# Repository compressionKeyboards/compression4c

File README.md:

# compression (4c)
PCB, ergogen, kicad files for 4c wireless split ergo keyboard

This repo contains the files to order a custom PCB for chocBoard, checkout the [zmk layout](https://github.com/compressionKeyboards/4c-zmk-layout) to build firmware!

Read more about chocBoard on [compression](https://compressionkeyboards.com).

## Downloads
feel free to dig around in my working files in the repo :) but if you just want to order a PCB or print a case, checkout the releases tab.

## TODO
Fusion and STEP files will be added soon, I'm just cleaning them up a bit. Also, display cover files are not final, and just a few dimensions will be tweaked in an upcoming release.

## LICENSE
This repo is attached with Attribution-NonCommercial-ShareAlike 4.0 International Creative Commons License, learn what his means [here](https://creativecommons.org/licenses/by-nc-sa/4.0/).

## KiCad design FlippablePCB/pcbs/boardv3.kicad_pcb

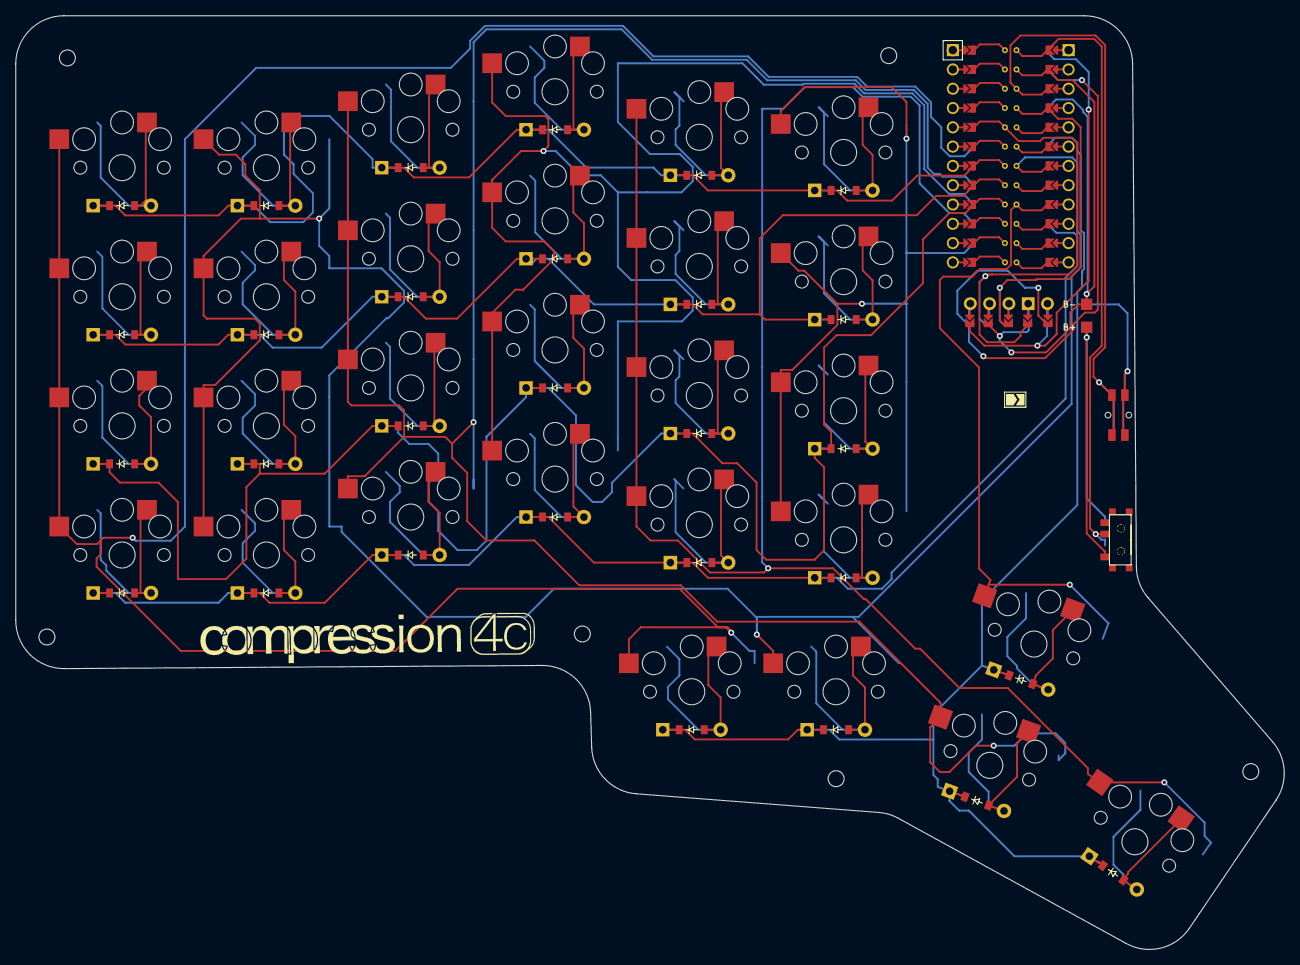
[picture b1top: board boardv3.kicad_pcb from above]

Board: 2 copper layers, 167.0 x 122.9 mm, 64 parts (0 on the bottom side), 43 nets.

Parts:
D1, D2, D3, D4, D5, D6, D7, D8, D9, D10, D11, D12, D13, D14, D15, D16, D17, D18, D19, D20, D21, D22, D23, D24, D25, D26, D27, D28, D29: ComboDiode
MCU1: ProMicro
OLED1: OLED; OLED_headers
PAD1, PAD2: SMDPad
S1, S2, S3, S4, S5, S6, S7, S8, S9, S10, S11, S12, S13, S14, S15, S16, S17, S18, S19, S20, S21, S22, S23, S24, S25, S26, S27, S28, S29: PG1350
T1, T2: SPDT_C128955

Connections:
Bplus: PAD1.1, T1.1, T2.1
GND: MCU1.2, MCU1.21, MCU1.22, PAD2.1
P3: D25.1, D26.1, D27.1, D28.1, D29.1, MCU1.19
P4: D4.1, D8.1, D12.1, D16.1, D20.1, D24.1, MCU1.18
P5: D3.1, D7.1, D11.1, D15.1, D19.1, D23.1, MCU1.17
P6: D2.1, D6.1, D10.1, D14.1, D18.1, D22.1, MCU1.16
P7: D1.1, D5.1, D9.1, D13.1, D17.1, D21.1, MCU1.15
P14: MCU1.10, S17.2, S18.2, S19.2, S20.2, S29.2
P15: MCU1.9, S13.2, S14.2, S15.2, S16.2, S28.2
P16: MCU1.11, S21.2, S22.2, S23.2, S24.2
P18: MCU1.8, S9.2, S10.2, S11.2, S12.2, S27.2
P19: MCU1.7, S5.2, S6.2, S7.2, S8.2, S26.2
P20: MCU1.6, S1.2, S2.2, S3.2, S4.2, S25.2
RAW: MCU1.1, T1.2, T2.2
far_home: D29.2, S29.1
home_home: D27.2, S27.1
home_top: D28.2, S28.1
index_bottom: D17.2, S17.1
index_home: D18.2, S18.1
index_num: D20.2, S20.1
index_top: D19.2, S19.1
inner_bottom: D21.2, S21.1
inner_home: D22.2, S22.1
inner_num: D24.2, S24.1
inner_top: D23.2, S23.1
middle_bottom: D13.2, S13.1
middle_home: D14.2, S14.1
middle_num: D16.2, S16.1
middle_top: D15.2, S15.1
near1_home: D25.2, S25.1
near2_home: D26.2, S26.1
outer_bottom: D1.2, S1.1
outer_home: D2.2, S2.1
outer_num: D4.2, S4.1
outer_top: D3.2, S3.1
pinky_bottom: D5.2, S5.1
pinky_home: D6.2, S6.1
pinky_num: D8.2, S8.1
pinky_top: D7.2, S7.1
ring_bottom: D9.2, S9.1
ring_home: D10.2, S10.1
ring_num: D12.2, S12.1
ring_top: D11.2, S11.1

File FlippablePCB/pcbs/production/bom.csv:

Designator,Footprint,Quantity,Value,LCSC Part #
"_24, _23, _22, _21, _20, _19, _18, _17, _16, _15, _14, _13, _12, _11, _10, _9, _8, _7, _6, _5, _4, _3, _2, ",,24,,
"D1, D10, D11, D12, D13, D14, D15, D16, D17, D18, D19, D2, D20, D21, D22, D23, D24, D25, D26, D27, D28, D29, D3, D4, D5, D6, D7, D8, D9",ComboDiode,29,,
MCU1,ProMicro,1,,
OLED1,OLED_headers,1,OLED,
"PAD1, PAD2",SMDPad,2,,
"S1, S10, S11, S12, S13, S14, S15, S16, S17, S18, S19, S2, S20, S21, S22, S23, S24, S25, S26, S27, S28, S29, S3, S4, S5, S6, S7, S8, S9",PG1350,29,,
"T1, T2",SPDT_C128955,2,,

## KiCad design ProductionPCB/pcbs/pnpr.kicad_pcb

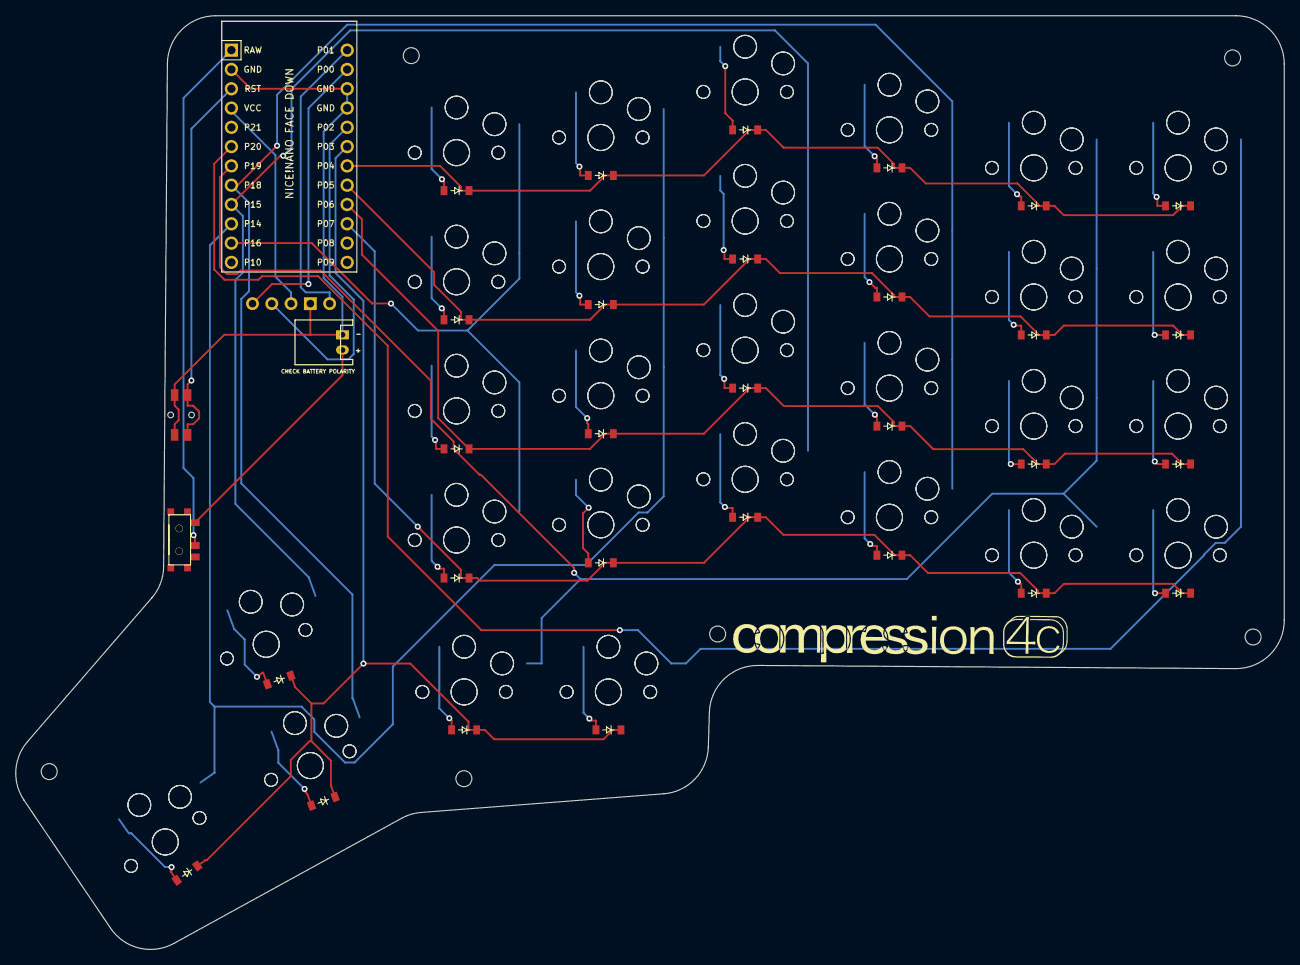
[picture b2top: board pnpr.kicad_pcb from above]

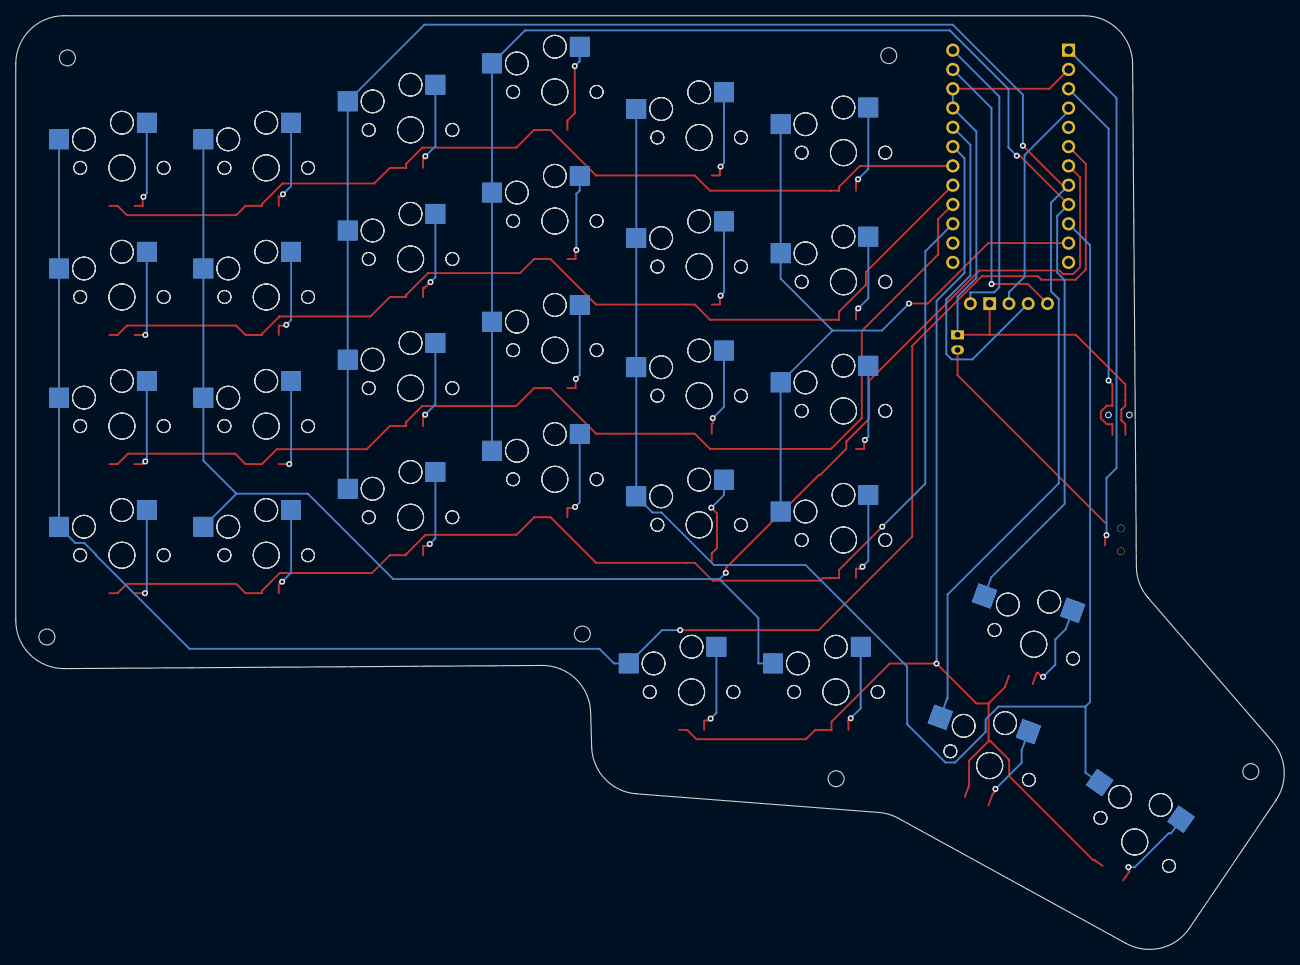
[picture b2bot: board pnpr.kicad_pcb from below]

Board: 2 copper layers, 167.0 x 122.9 mm, 92 parts (29 on the bottom side), 44 nets.

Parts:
D31, D34, D36, D37, D41, D49, D51, D52, D53, D54, D57, D58, D59, D61, D62, D64, D67, D68, D69, D71, D72, D73, D74, D75, D76, D77, D79, D84, D85: ComboDiode
JST1: JST_PH_S2B-PH-K_02x2.00mm_Angled
MCU1: ProMicro
OLED1: OLED; OLED_headers
Panasonic_EVQPUL_EVQPUC: Panasonic_EVQPUL_EVQPUC
S30, S31, S32, S33, S34, S35, S36, S37, S38, S39, S40, S41, S42, S43, S44, S45, S46, S47, S48, S49, S50, S51, S52, S53, S54, S55, S56, S57, S58, S59, S60, S61, S62, S63, S64, S65, S66, S67, S68, S69, S70, S71, S72, S73, S74, S75, S76, S77, S78, S79, S80, S81, S82, S83, S84, S85, S86, S87: PG1350
T1: SPDT_C128955

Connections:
Bplus: JST1.2, T1.1
GND: JST1.1, MCU1.2, MCU1.15, MCU1.16, Panasonic_EVQPUL_EVQPUC.1
P3: D54.1, D57.1, D58.1, D84.1, D85.1, MCU1.18
P4: D37.1, D41.1, D49.1, D53.1, D62.1, D74.1, MCU1.19
P5: D36.1, D52.1, D61.1, D69.1, D73.1, D77.1, MCU1.20
P6: D31.1, D51.1, D64.1, D68.1, D72.1, D76.1, MCU1.21
P7: D34.1, D59.1, D67.1, D71.1, D75.1, D79.1, MCU1.22
P14: MCU1.10, S46.2, S47.2, S48.2, S49.2, S58.2, S75.2, S76.2, S77.2, S78.2, S87.2
P15: MCU1.9, S42.2, S43.2, S44.2, S45.2, S57.2, S71.2, S72.2, S73.2, S74.2, S86.2
P16: MCU1.11, S50.2, S51.2, S52.2, S53.2, S79.2, S80.2, S81.2, S82.2
P18: MCU1.8, S38.2, S39.2, S40.2, S41.2, S56.2, S67.2, S68.2, S69.2, S70.2, S85.2
P19: MCU1.7, S34.2, S35.2, S36.2, S37.2, S55.2, S63.2, S64.2, S65.2, S66.2, S84.2
P20: MCU1.6, S30.2, S31.2, S32.2, S33.2, S54.2, S59.2, S60.2, S61.2, S62.2, S83.2
RAW: MCU1.1, T1.2
RST: MCU1.3, Panasonic_EVQPUL_EVQPUC.2
mirror_far_home: D58.2, S58.1, S87.1
mirror_home_home: D85.2, S56.1, S85.1
mirror_home_top: D57.2, S57.1, S86.1
mirror_index_bottom: D75.2, S46.1, S75.1
mirror_index_home: D76.2, S47.1, S76.1
mirror_index_num: D49.2, S49.1, S78.1
mirror_index_top: D77.2, S48.1, S77.1
mirror_inner_bottom: D79.2, S50.1, S79.1
mirror_inner_home: D51.2, S51.1, S80.1
mirror_inner_num: D53.2, S53.1, S82.1
mirror_inner_top: D52.2, S52.1, S81.1
mirror_middle_bottom: D71.2, S42.1, S71.1
mirror_middle_home: D72.2, S43.1, S72.1
mirror_middle_num: D74.2, S45.1, S74.1
mirror_middle_top: D73.2, S44.1, S73.1
mirror_near1_home: D54.2, S54.1, S83.1
mirror_near2_home: D84.2, S55.1, S84.1
mirror_outer_bottom: D59.2, S30.1, S59.1
mirror_outer_home: D31.2, S31.1, S60.1
mirror_outer_num: D62.2, S33.1, S62.1
mirror_outer_top: D61.2, S32.1, S61.1
mirror_pinky_bottom: D34.2, S34.1, S63.1
mirror_pinky_home: D64.2, S35.1, S64.1
mirror_pinky_num: D37.2, S37.1, S66.1
mirror_pinky_top: D36.2, S36.1, S65.1
mirror_ring_bottom: D67.2, S38.1, S67.1
mirror_ring_home: D68.2, S39.1, S68.1
mirror_ring_num: D41.2, S41.1, S70.1
mirror_ring_top: D69.2, S40.1, S69.1

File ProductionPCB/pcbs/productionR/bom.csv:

Designator,Footprint,Quantity,Value,LCSC Part #
"D31, D34, D36, D37, D41, D49, D51, D52, D53, D54, D57, D58, D59, D61, D62, D64, D67, D68, D69, D71, D72, D73, D74, D75, D76, D77, D79, D84, D85",ComboDiode,29,,C109203
JST1,JST_PH_S2B-PH-K_02x2.00mm_Angled,1,,C157932
MCU1,ProMicro,0,,
OLED1,OLED_headers,1,OLED,C2889987
Panasonic_EVQPUL_EVQPUC,Panasonic_EVQPUL_EVQPUC,1,Panasonic_EVQPUL_EVQPUC,C79174
"S30, S31, S32, S33, S34, S35, S36, S37, S38, S39, S40, S41, S42, S43, S44, S45, S46, S47, S48, S49, S50, S51, S52, S53, S54, S55, S56, S57, S58, S59, S60, S61, S62, S63, S64, S65, S66, S67, S68, S69, S70, S71, S72, S73, S74, S75, S76, S77, S78, S79, S80, S81, S82, S83, S84, S85, S86, S87",PG1350,0,,
T1,SPDT_C128955,1,,C128955

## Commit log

2023-07-26 init
2023-08-22 rev 1.1
